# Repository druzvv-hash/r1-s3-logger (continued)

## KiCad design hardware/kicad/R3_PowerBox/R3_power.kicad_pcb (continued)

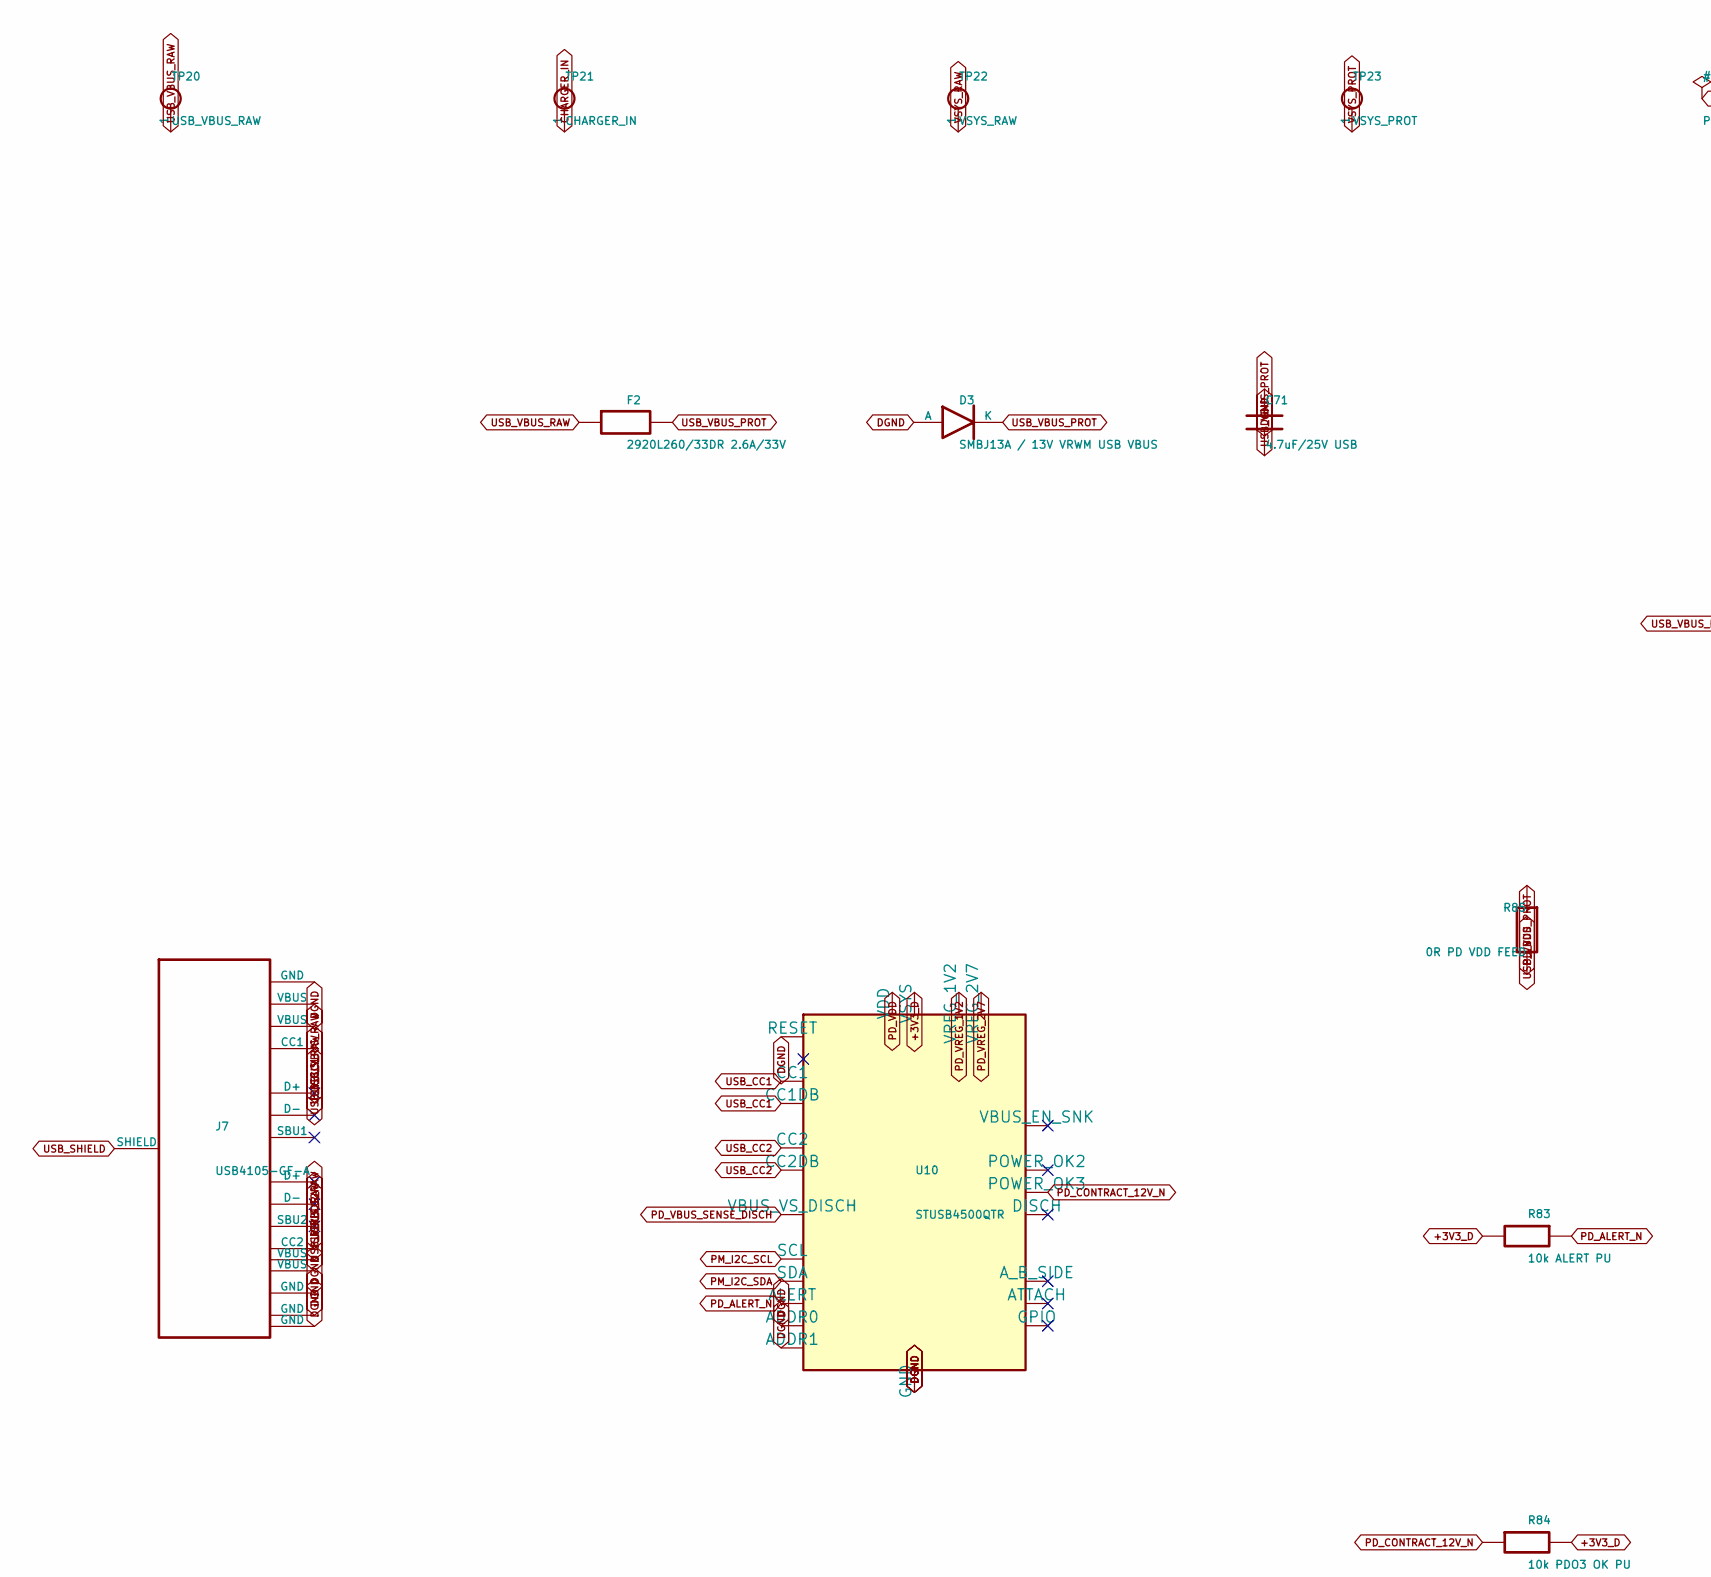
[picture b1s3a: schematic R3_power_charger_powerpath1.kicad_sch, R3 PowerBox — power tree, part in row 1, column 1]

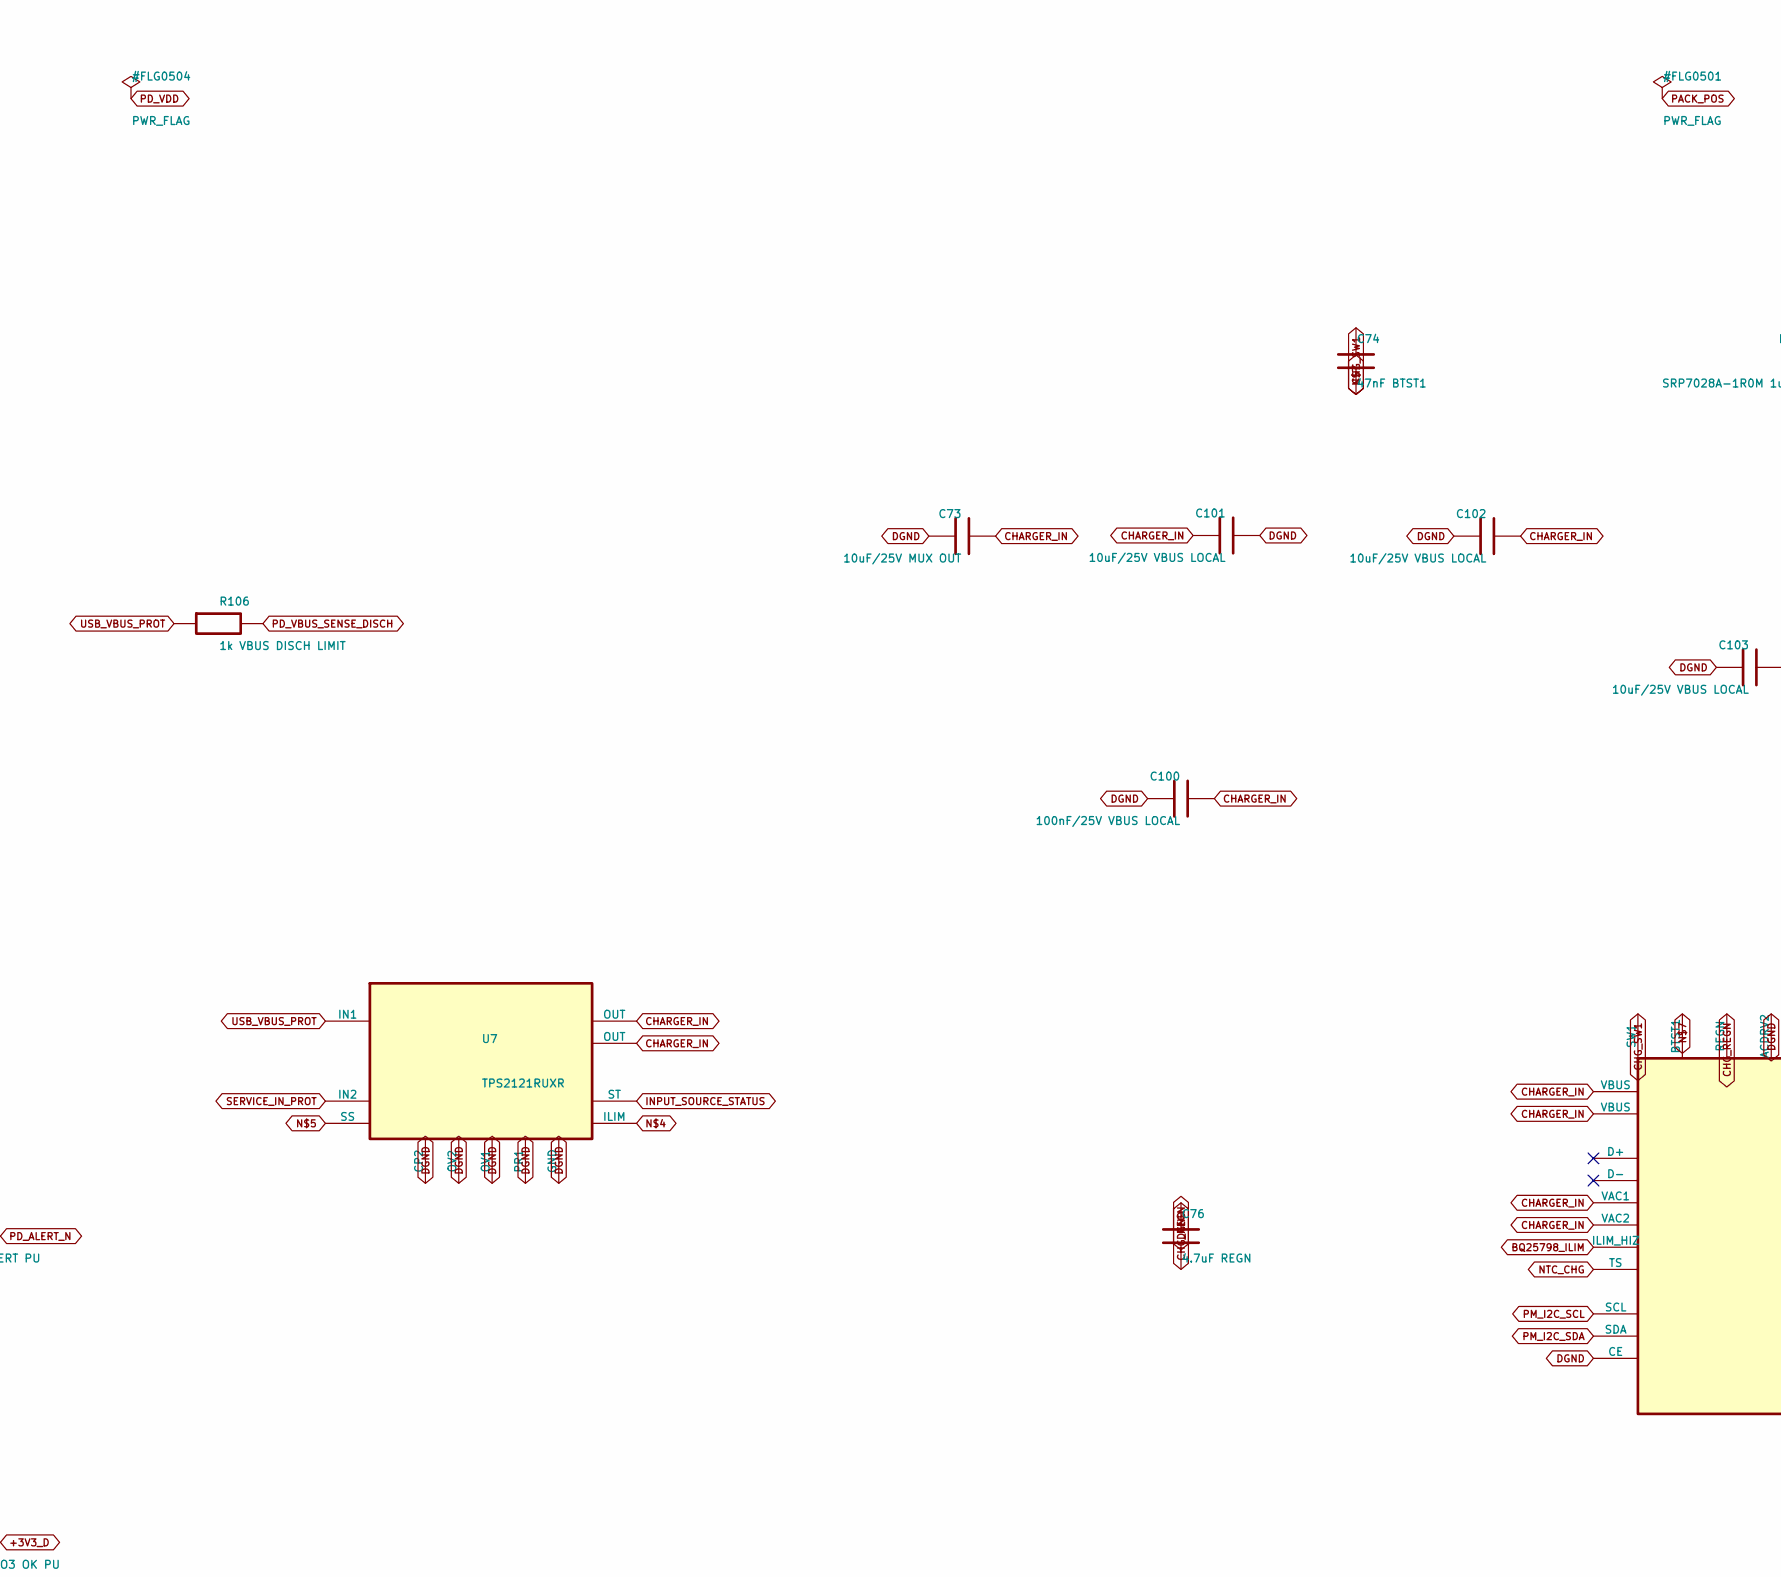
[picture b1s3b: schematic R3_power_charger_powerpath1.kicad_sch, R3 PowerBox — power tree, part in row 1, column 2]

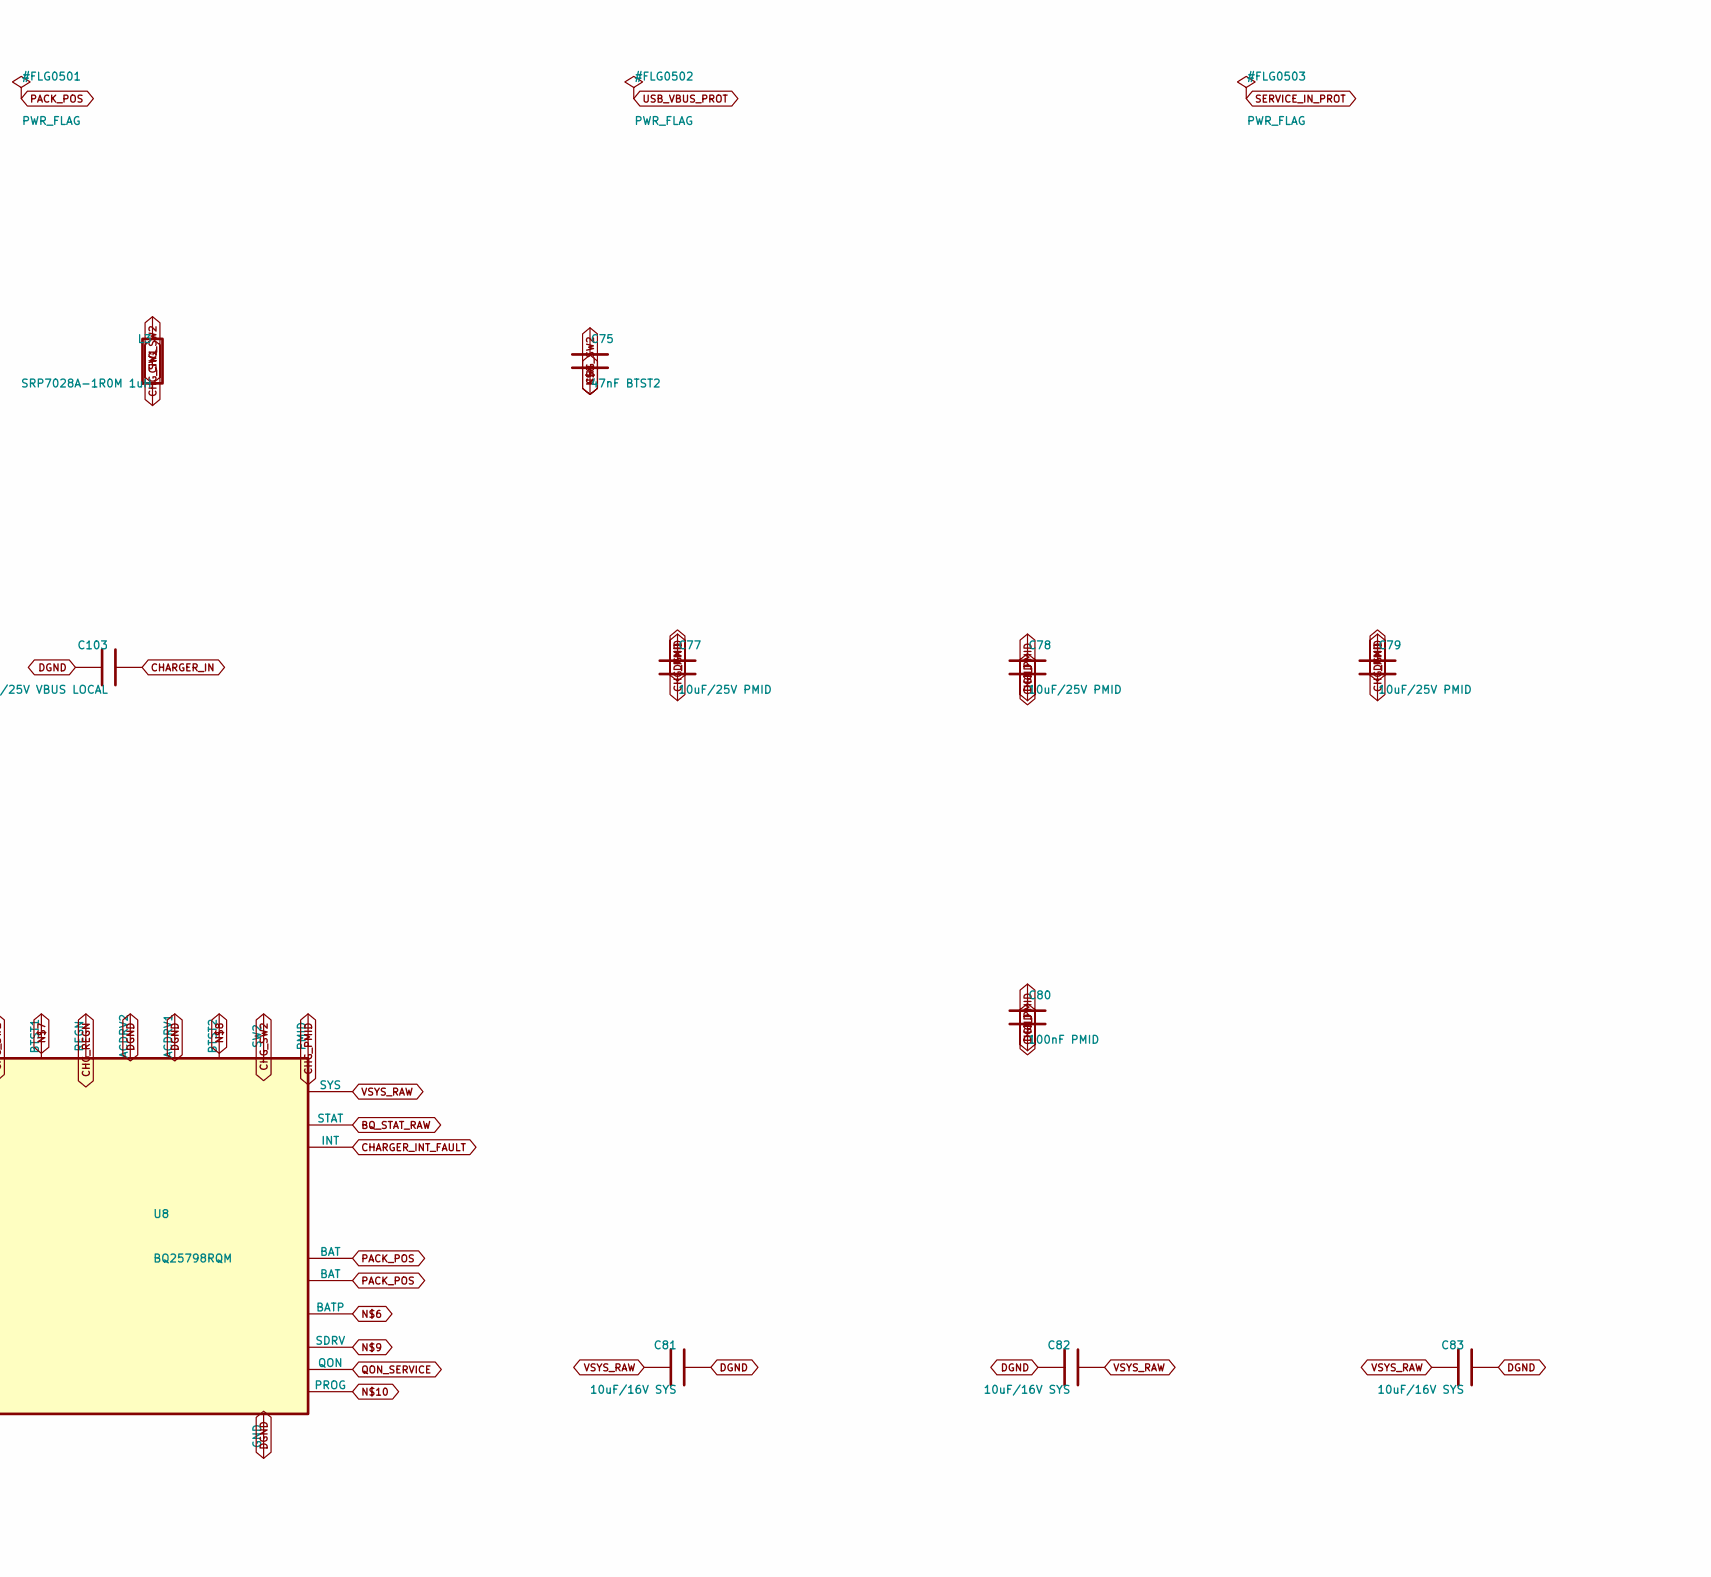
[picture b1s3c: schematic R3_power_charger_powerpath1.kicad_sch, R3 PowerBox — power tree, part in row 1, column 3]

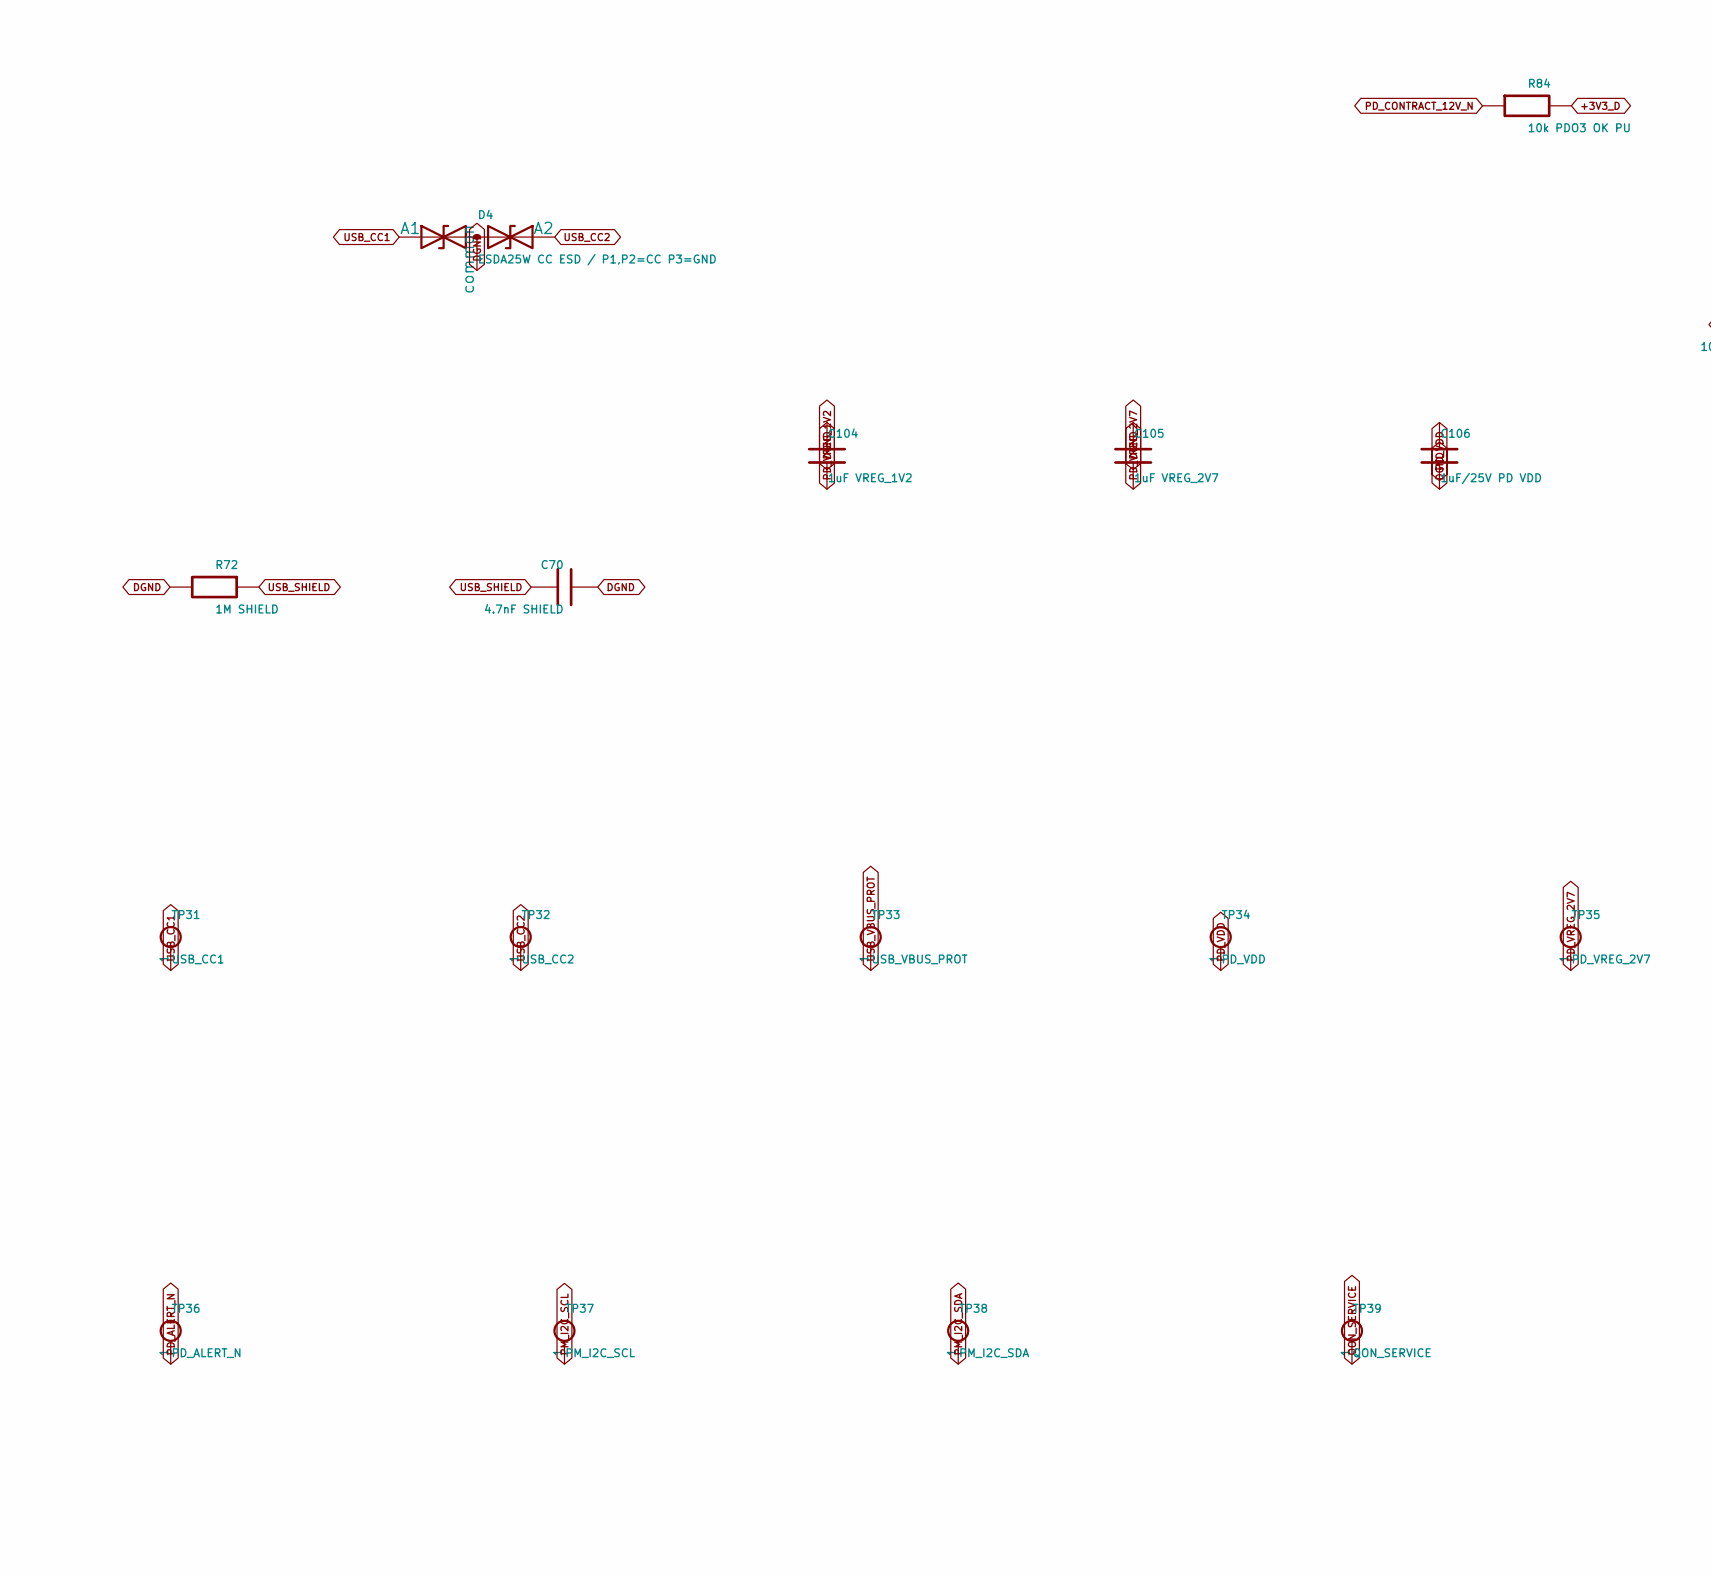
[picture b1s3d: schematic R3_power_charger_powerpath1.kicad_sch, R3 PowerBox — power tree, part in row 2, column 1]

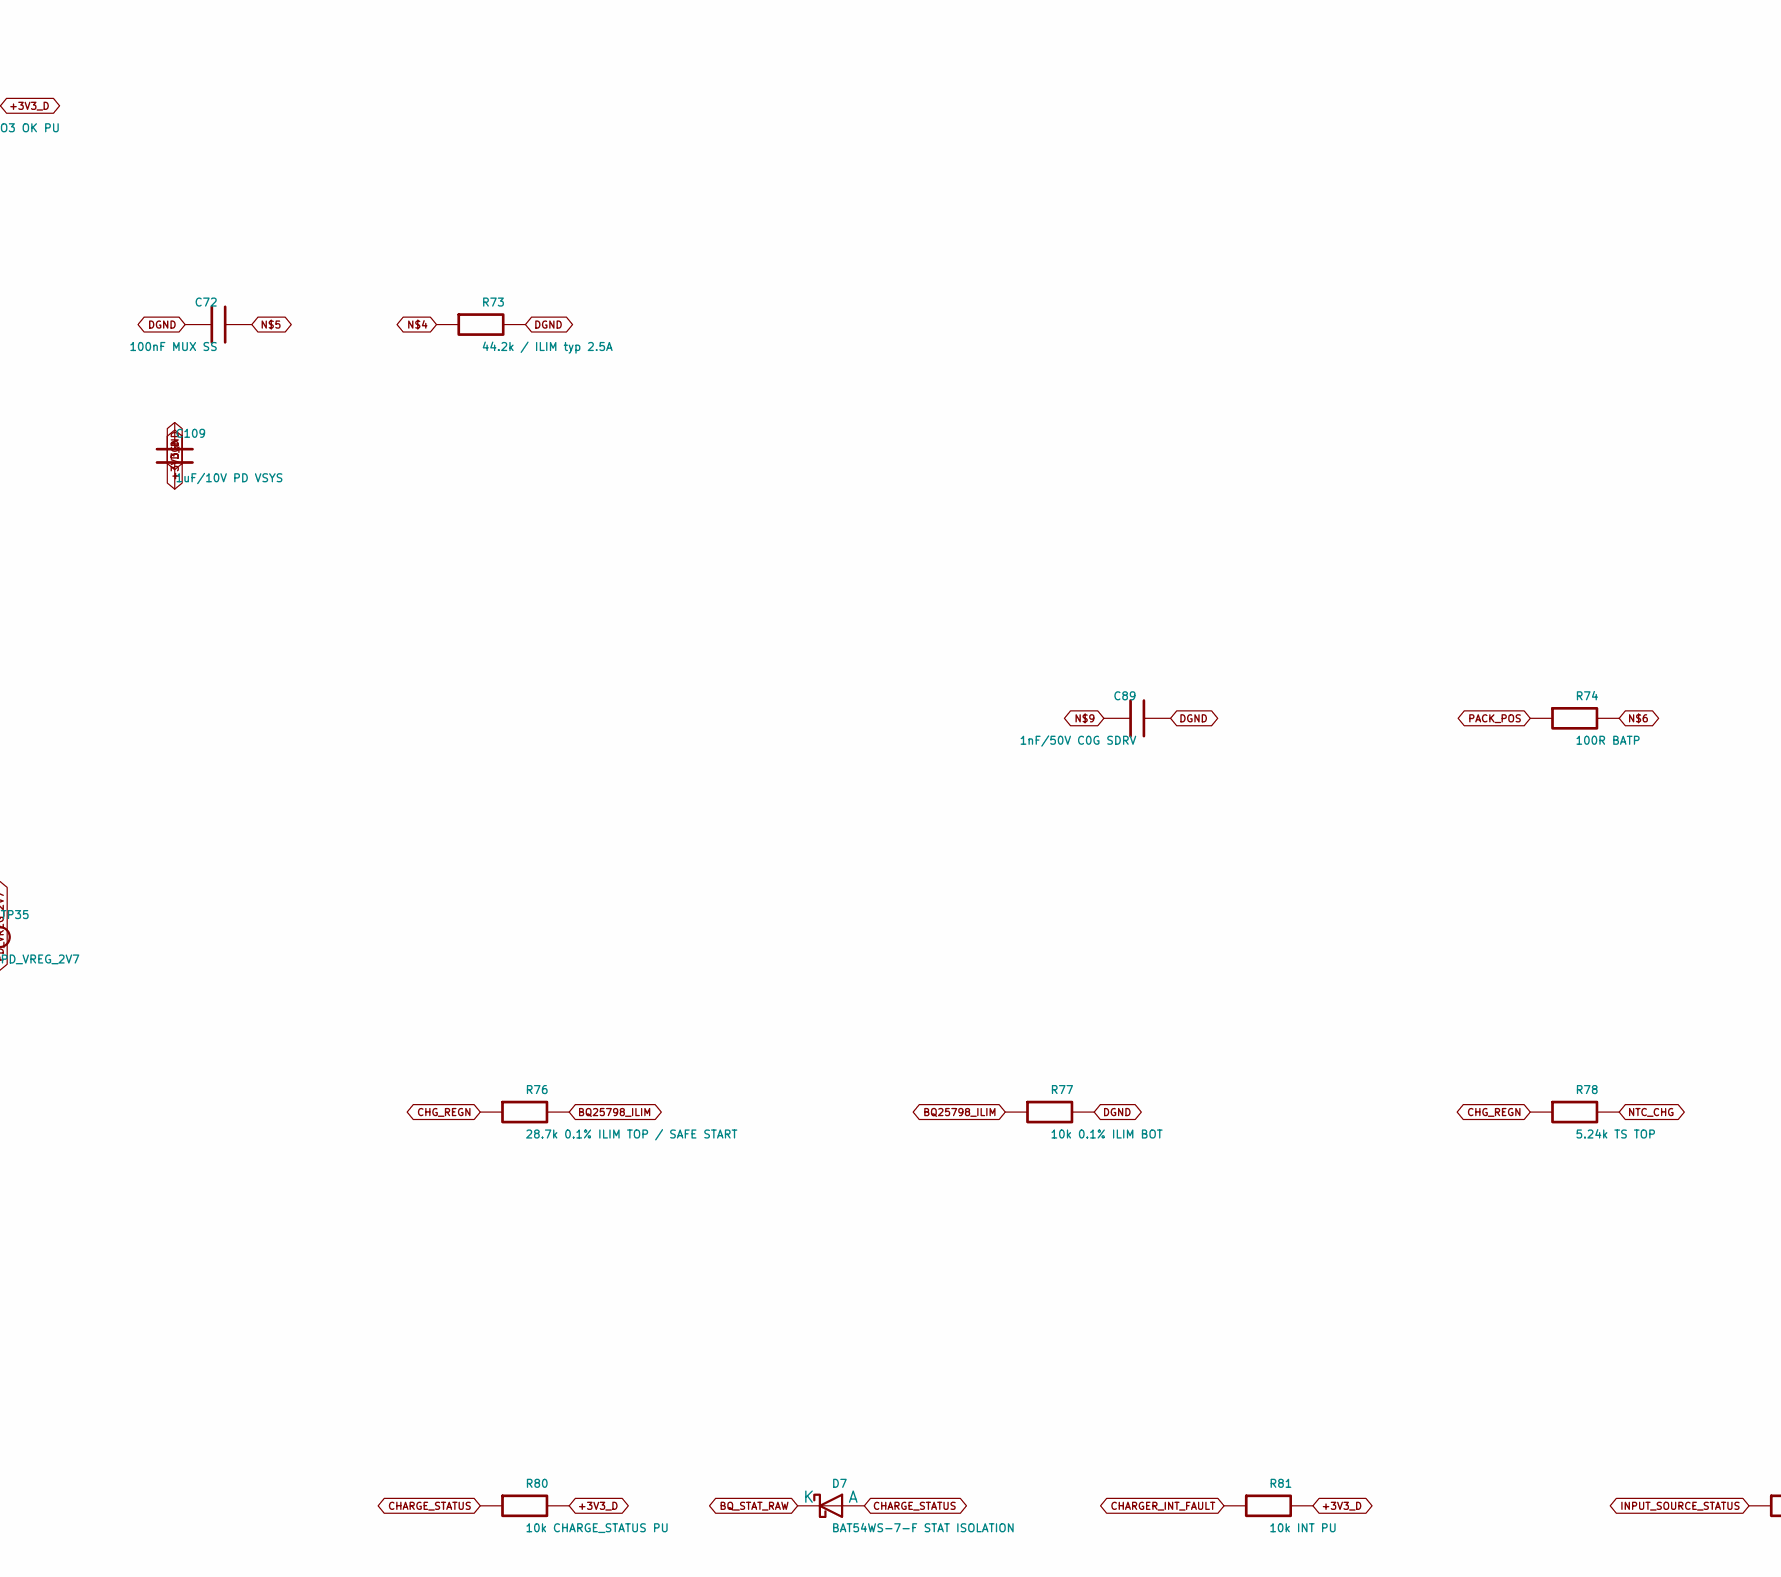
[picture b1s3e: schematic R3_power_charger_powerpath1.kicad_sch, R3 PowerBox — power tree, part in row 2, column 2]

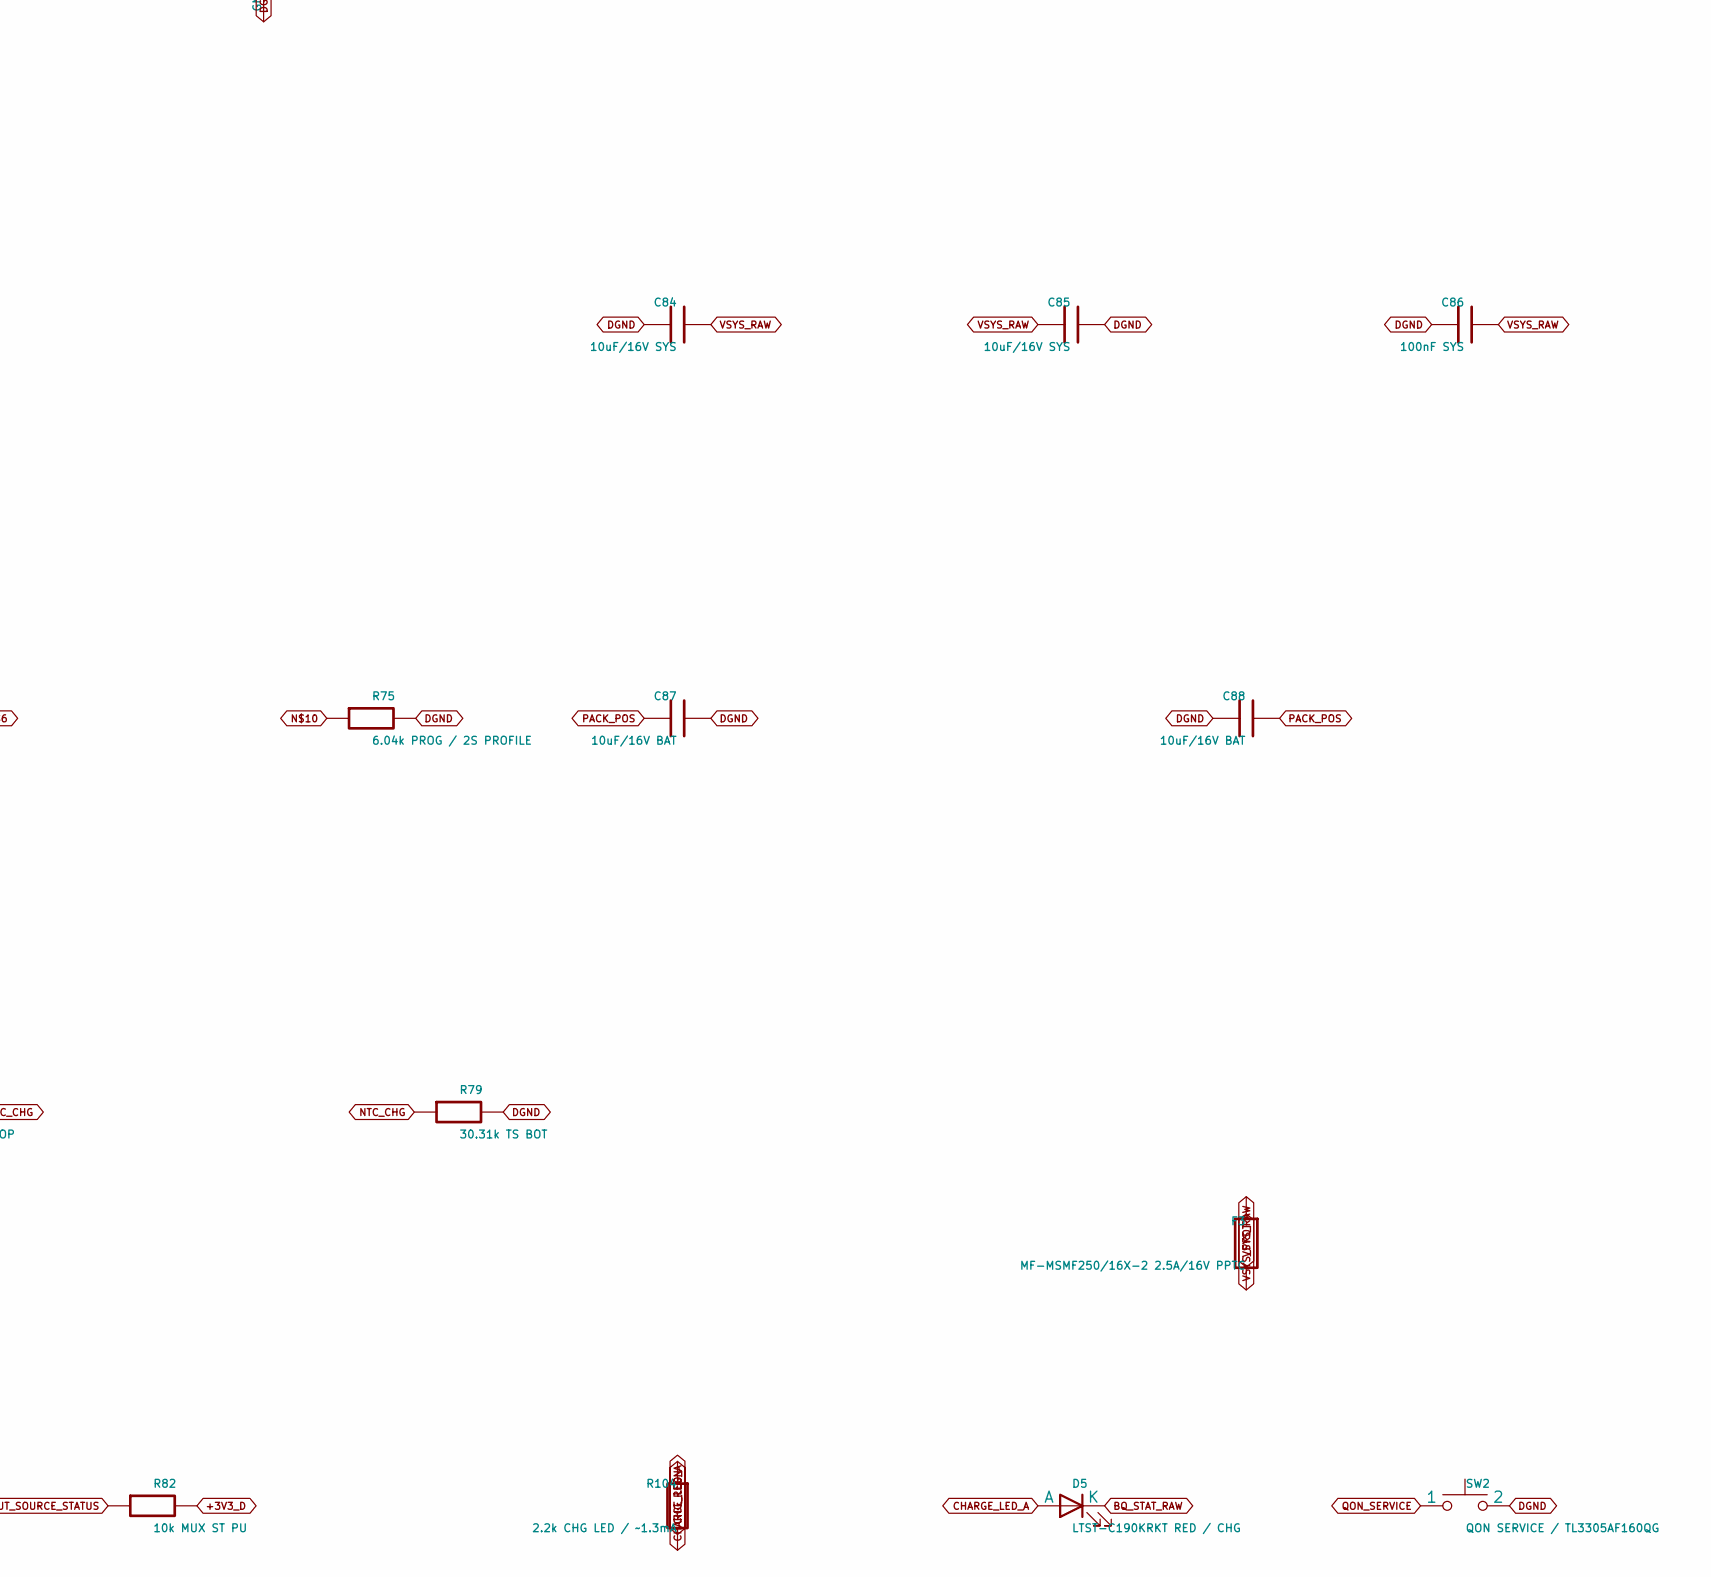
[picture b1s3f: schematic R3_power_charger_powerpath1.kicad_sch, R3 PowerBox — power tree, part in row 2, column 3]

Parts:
C70: 4.7nF SHIELD; C_0603_1608Metric
C71: 4.7uF/25V USB; C_1206_3216Metric
C72: 100nF MUX SS; C_0603_1608Metric
C73: 10uF/25V MUX OUT; C_1206_3216Metric
C74: 47nF BTST1; C_0603_1608Metric
C75: 47nF BTST2; C_0603_1608Metric
C76: 4.7uF REGN; C_0603_1608Metric
C77, C78, C79: 10uF/25V PMID; C_1206_3216Metric
C80: 100nF PMID; C_0603_1608Metric
C81, C82, C83, C84, C85: 10uF/16V SYS; C_1206_3216Metric
C86: 100nF SYS; C_0603_1608Metric
C87, C88: 10uF/16V BAT; C_1206_3216Metric
C89: 1nF/50V C0G SDRV; C_0603_1608Metric
C100: 100nF/25V VBUS LOCAL; C_0402_1005Metric
C101, C102, C103: 10uF/25V VBUS LOCAL; C_1206_3216Metric
C104: 1uF VREG_1V2; C_0603_1608Metric
C105: 1uF VREG_2V7; C_0603_1608Metric
C106: 1uF/25V PD VDD; C_0603_1608Metric
C109: 1uF/10V PD VSYS; C_0402_1005Metric
D3: SMBJ13A / 13V VRWM USB VBUS; D_SMB
D4: ESDA25W CC ESD / P1,P2=CC P3=GND; SOT-323_SC-70
D5: LTST-C190KRKT RED / CHG; LED_0603_1608Metric
D7: BAT54WS-7-F STAT ISOLATION; D_SOD-323
F2: 2920L260/33DR 2.6A/33V; Fuse_2920_7451Metric
F3: MF-MSMF250/16X-2 2.5A/16V PPTC; Fuse_1812_4532Metric_Pad1.30x3.40mm_HandSolder
J7: USB4105-GF-A; USB_C_Receptacle_GCT_USB4105-xx-A_16P_TopMnt_Horizontal
L3: SRP7028A-1R0M 1uH; L_Bourns_SRP7028A_7.3x6.6mm
R72: 1M SHIELD; R_0603_1608Metric
R73: 44.2k / ILIM typ 2.5A; R_0603_1608Metric
R74: 100R BATP; R_0603_1608Metric
R75: 6.04k PROG / 2S PROFILE; R_0603_1608Metric
R76: 28.7k 0.1% ILIM TOP / SAFE START; R_0603_1608Metric
R77: 10k 0.1% ILIM BOT; R_0603_1608Metric
R78: 5.24k TS TOP; R_0603_1608Metric
R79: 30.31k TS BOT; R_0603_1608Metric
R80: 10k CHARGE_STATUS PU; R_0603_1608Metric
R81: 10k INT PU; R_0603_1608Metric
R82: 10k MUX ST PU; R_0603_1608Metric
R83: 10k ALERT PU; R_0603_1608Metric
R84: 10k PDO3 OK PU; R_0603_1608Metric
R85: 0R PD VDD FEED; R_0603_1608Metric
R104: 2.2k CHG LED / ~1.3mA; R_0603_1608Metric
R106: 1k VBUS DISCH LIMIT; R_0603_1608Metric
SW2: QON SERVICE / TL3305AF160QG; SW_SPST_TL3305A
TP20: USB_VBUS_RAW; TestPoint_Plated_Hole_D2.0mm
TP21: CHARGER_IN; TestPoint_Plated_Hole_D2.0mm
TP22: VSYS_RAW; TestPoint_Plated_Hole_D2.0mm
TP23: VSYS_PROT; TestPoint_Plated_Hole_D2.0mm
TP31: USB_CC1; TestPoint_CC_D0.6mm
TP32: USB_CC2; TestPoint_CC_D0.6mm
TP33: USB_VBUS_PROT; TestPoint_Plated_Hole_D2.0mm
TP34: PD_VDD; TestPoint_Plated_Hole_D2.0mm
TP35: PD_VREG_2V7; TestPoint_Plated_Hole_D2.0mm
TP36: PD_ALERT_N; TestPoint_Plated_Hole_D2.0mm
TP37: PM_I2C_SCL; TestPoint_Plated_Hole_D2.0mm
TP38: PM_I2C_SDA; TestPoint_Plated_Hole_D2.0mm
TP39: QON_SERVICE; TestPoint_Plated_Hole_D2.0mm
U7: TPS2121RUXR; Texas_VQFN-HR-12_2x2.5mm_P0.5mm
U8: BQ25798RQM; Texas_RQM0029A_VQFN-29_4x4mm_P0.4mm
U10: STUSB4500QTR; QFN-24-1EP_4x4mm_P0.5mm_EP2.7x2.7mm

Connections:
+3V3_D: C109.1, R80.2, R81.2, R82.2, R83.2, R84.2, U10.22 (VSYS); also elsewhere on the board
BQ25798_ILIM: R76.2, R77.1, U8.17 (ILIM_HIZ)
BQ_STAT_RAW: D5.1 (K), D7.1 (K), U8.1 (STAT); also elsewhere on the board
CHARGER_IN: C73.1, C100.1, C101.1, C102.1, C103.1, TP21.1, U7.1 (OUT), U7.8 (OUT), U8.2 (VBUS), U8.3 (VBUS), U8.8 (VAC2), U8.9 (VAC1)
CHARGER_INT_FAULT: R81.1, U8.21 (INT); also elsewhere on the board
CHARGE_LED_A: D5.2 (A), R104.2
CHARGE_STATUS: D7.2 (A), R80.1; also elsewhere on the board
CHG_PMID: C77.1, C78.1, C79.1, C80.1, U8.29 (PMID)
CHG_REGN: C76.1, R76.1, R78.1, R104.1, U8.5 (REGN)
CHG_SW1: C74.2, L3.1, U8.28 (SW1)
CHG_SW2: C75.2, L3.2, U8.26 (SW2)
DGND: C70.2, C71.2, C72.2, C73.2, C76.2, C77.2, C78.2, C79.2, C80.2, C81.2, C82.2, C83.2, C84.2, C85.2, C86.2, C87.2, C88.2, C89.2, C100.2, C101.2, C102.2, C103.2, C104.2, C105.2, C106.2, C109.2, D3.2 (A), D4.3 (common), J7.A1 (GND), J7.A12 (GND), J7.B1 (GND), J7.B12 (GND), R72.2, R73.2, R75.2, R77.2, R79.2, SW2.2, U7.3 (CP2), U7.4 (OV2), U7.5 (OV1), U7.6 (PR1), U7.12 (GND), U8.10 (ACDRV2), U8.11 (ACDRV1), U8.13 (CE), U8.27 (GND), U10.6 (RESET), U10.10 (GND), U10.12 (ADDR0), U10.13 (ADDR1), U10.25 (GND); also elsewhere on the board
INPUT_SOURCE_STATUS: R82.1, U7.9 (ST); also elsewhere on the board
unnamed: R73.1, U7.10 (ILIM)
unnamed: C72.1, U7.11 (SS)
unnamed: R74.2, U8.18 (BATP)
unnamed: C74.1, U8.4 (BTST1)
unnamed: C75.1, U8.19 (BTST2)
unnamed: C89.1, U8.24 (SDRV)
unnamed: R75.1, U8.20 (PROG)
NTC_CHG: R78.2, R79.1, U8.16 (TS); also elsewhere on the board
PACK_POS: C87.1, C88.1, R74.1, U8.22 (BAT), U8.23 (BAT); also elsewhere on the board
PD_ALERT_N: R83.1, TP36.1, U10.19 (ALERT); also elsewhere on the board
PD_CONTRACT_12V_N: R84.1, U10.14 (POWER_OK3); also elsewhere on the board
PD_VBUS_SENSE_DISCH: R106.2, U10.18 (VBUS_VS_DISCH)
PD_VDD: C106.1, R85.2, TP34.1, U10.24 (VDD)
PD_VREG_1V2: C104.1, U10.21 (VREG_1V2)
PD_VREG_2V7: C105.1, TP35.1, U10.23 (VREG_2V7)
PM_I2C_SCL: TP37.1, U8.14 (SCL), U10.7 (SCL); also elsewhere on the board
PM_I2C_SDA: TP38.1, U8.15 (SDA), U10.8 (SDA); also elsewhere on the board
QON_SERVICE: SW2.1, TP39.1, U8.12 (QON); also elsewhere on the board
SERVICE_IN_PROT: U7.2 (IN2); also elsewhere on the board
USB_CC1: D4.1 (A1), J7.A5 (CC1), TP31.1, U10.1 (CC1DB), U10.2 (CC1)
USB_CC2: D4.2 (A2), J7.B5 (CC2), TP32.1, U10.4 (CC2), U10.5 (CC2DB)
USB_SHIELD: C70.1, J7.SH (SHIELD), R72.1
USB_VBUS_PROT: C71.1, D3.1 (K), F2.2, R85.1, R106.1, TP33.1, U7.7 (IN1)
USB_VBUS_RAW: F2.1, J7.A4 (VBUS), J7.A9 (VBUS), J7.B4 (VBUS), J7.B9 (VBUS), TP20.1
VSYS_PROT: F3.2, TP23.1; also elsewhere on the board
VSYS_RAW: C81.1, C82.1, C83.1, C84.1, C85.1, C86.1, F3.1, TP22.1, U8.25 (SYS)

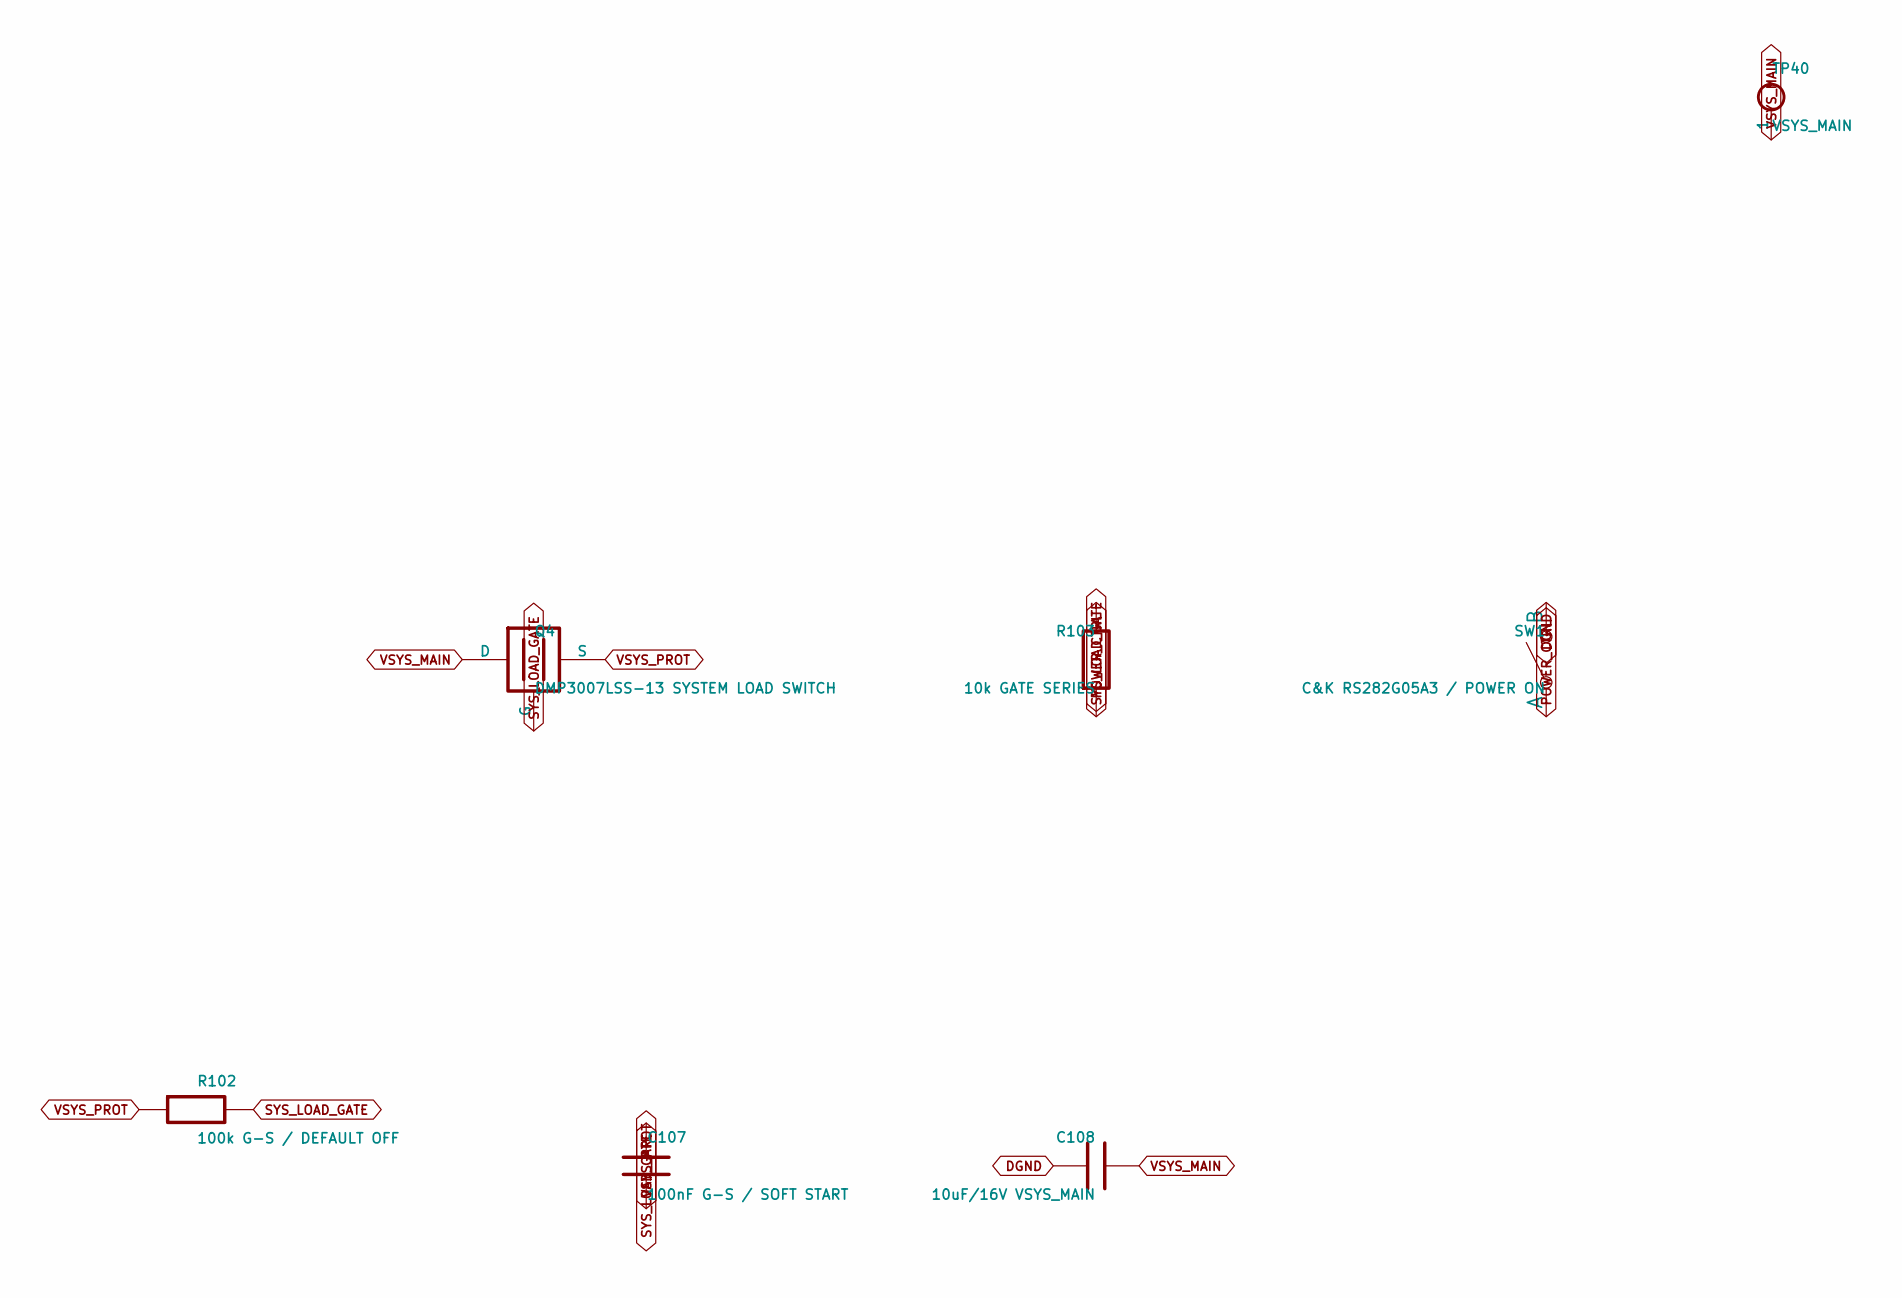
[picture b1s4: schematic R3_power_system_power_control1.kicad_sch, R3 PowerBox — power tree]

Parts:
C107: 100nF G-S / SOFT START; C_0603_1608Metric
C108: 10uF/16V VSYS_MAIN; C_1206_3216Metric
Q4: DMP3007LSS-13 SYSTEM LOAD SWITCH; DMP3007LSS_SO8_LOGICAL
R102: 100k G-S / DEFAULT OFF; R_0603_1608Metric
R103: 10k GATE SERIES; R_0603_1608Metric
SW1: C&K RS282G05A3 / POWER ON; SW_SPST_CK_RS282G05A3
TP40: VSYS_MAIN; TestPoint_Plated_Hole_D2.0mm

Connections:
DGND: C108.2, SW1.2 (B); also elsewhere on the board
POWER_CTRL: R103.2, SW1.1 (A); also elsewhere on the board
SYS_LOAD_GATE: C107.2, Q4.1 (G), R102.2, R103.1
VSYS_MAIN: C108.1, Q4.3 (D), TP40.1; also elsewhere on the board
VSYS_PROT: C107.1, Q4.2 (S), R102.1; also elsewhere on the board
